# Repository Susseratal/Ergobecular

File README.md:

# Ergobecular Readme

## The Ergobecular  
The Ergobecular is a layout for a customisable, ergonomic mechanical keyboard. While it's based on my personal layout and preferences, it's designed to be configured and customised to the needs and preferences of you, the user.  
One of the primary choices made is to focus on smaller key sizes, never going above 1.5 unit keys. This way, stabilisers are completely unneeded, which will make tuning them for acoustics much easier. 

The main choice will be whether you want a split board, or a plank. In the future, I'd like to create a kind of Alice like design, but for the time being these will be the two main options.  
In the split category, you'll also be able to choose between columnar and fully ortholinear, while the plank will just be fully ortho for standard case compatibility.  
You'll also need to choose whether you want MX compatible sockets, or Kailh choc compatible sockets. 

Once I've finished making the designs, you should be able to just grab the PCB files you want from this repo and upload them to your PCB manufacturer of choice.  
Finally, I'll have not only firmware source files for you to start from, I'll also have a precompiled hex file for you to flash straight to the board if you don't have QMK configured, and don't mind using my layout. 

When the project is further along, a proper build guide will be available here as well. 

## The EBSplit  
The split version of the Ergobecular is probably the most customisable, as not only does it have options for all the different switches, you can also choose between columnar or fully ortho.  

This version of the board is likely going to be more ergonomic than the plank version, and more versatile if you've got the setup to handle it, but less portable.  
It'll need an extra TRRS cable to connect the halves, and you'll have to remember to carry around both halves of it, plus additional unpacking time.  
If you're the type of person who moves between home and the office, this might not be the way to go. 

I'd like to include a small screen for displaying information in this version, as I like the idea of having it pull system time, as well as displaying layer information.  
I think it could even be used for fun little gimmicks like a compass or something, I'm not sure. Being programmable, I'm sure people will be able to think of some fun stuff to do with this. 

## The EBPlank  
The plank version is designed either for someone who's not so fussed about a split design, or has a greater need for portability.  
While a split keyboard is portable, you can't quite throw it into a bag the same way you can with a regular keyboard.  

Because of this, as well as the slightly larger form factor, I see this as being a slightly more beginner friendly variant of the board.  
A stepping stone for someone who's tentatively interested in building their own keyboard, and wants to try a non-staggered layout, but isn't fully ready to commit to the split.  
This will also help someone get more used to designing their own layouts, although it would definitely be easier to get a ZSA keyboard, as their online layout tool is excellent, and very easy to use. 

I'm going to build one of these myself so that I can take it with me when I go away so I won't have to switch back to a more standard keyboard.  
Although that does mean I'm probably going to have to put silent switches in it.  

This will also be designed for compatibility with a lot of generic 60% cases, as this is a 60% keeb, rather than the split variant which is closer to a 40%.  
The case I'll be using for reference is a Miller GM862 which I've got sat on my shelf, but I'm going to try and include screw holes in standard places where possible.  
If you run into any issues with aftermarket cases, please send me an email to let me know.  
If it's just a one off thing I can't promise I'll be able to do much, but if I get multiple people telling me it doesn't fit common cases I'll definitely see what i can do. 

## Firmware  
The firmware has moved! I'm no longer keeping my firmware source here, rather I am including the source, as well as the precompiled binaries for all my keyboard layouts in [my own fork of the QMK firmware](https://github.com/susseratal/qmk_firmware)! 

My Ergodox is the Shine variant, so if you have the Glow or non LED variants, it might be prudent to download the necessary firmware and do a diff to see where changes need to be made.  
Also if you've got a Moonlander, you might also have to make some tweaks to the layout in order to make it work. I've been meaning to make versions of my layout for these keyboards too, but it's just a matter of finding the time. 

The difference between my firmware, and the version of my Ergodox layout available on ZSA's online configurator is that I've got a set of custom macro functions to make typing and editing text more "vim" like. The Oryx configurator does not, unfortunately, have support for layer switch on macro.  

My standard for laying out the firmware is that each column should be 3 spaces away from the longest line on the previous column. This should make it easier to read.  

## Todo:  
 
        - [ ] Design variants for 
                - [ ] split columnar MX 
                - [ ] split ortho MX
                - [ ] split columnar Choc
                - [ ] split ortho Choc
                - [ ] Plank MX
                - [ ] Plank Choc
        - [ ] Design and compile firmware for all of these
        - [ ] Design cases and plates for 3D printing

## Done:

        - [x] Write a design brief
        - [x] Custom qmk fork :)

Please do get in touch and let me know what you think of the designs and if you've used any of them. (when they're done of course) Feedback is always appreciated. 

Cheers,  
~ Iain xx

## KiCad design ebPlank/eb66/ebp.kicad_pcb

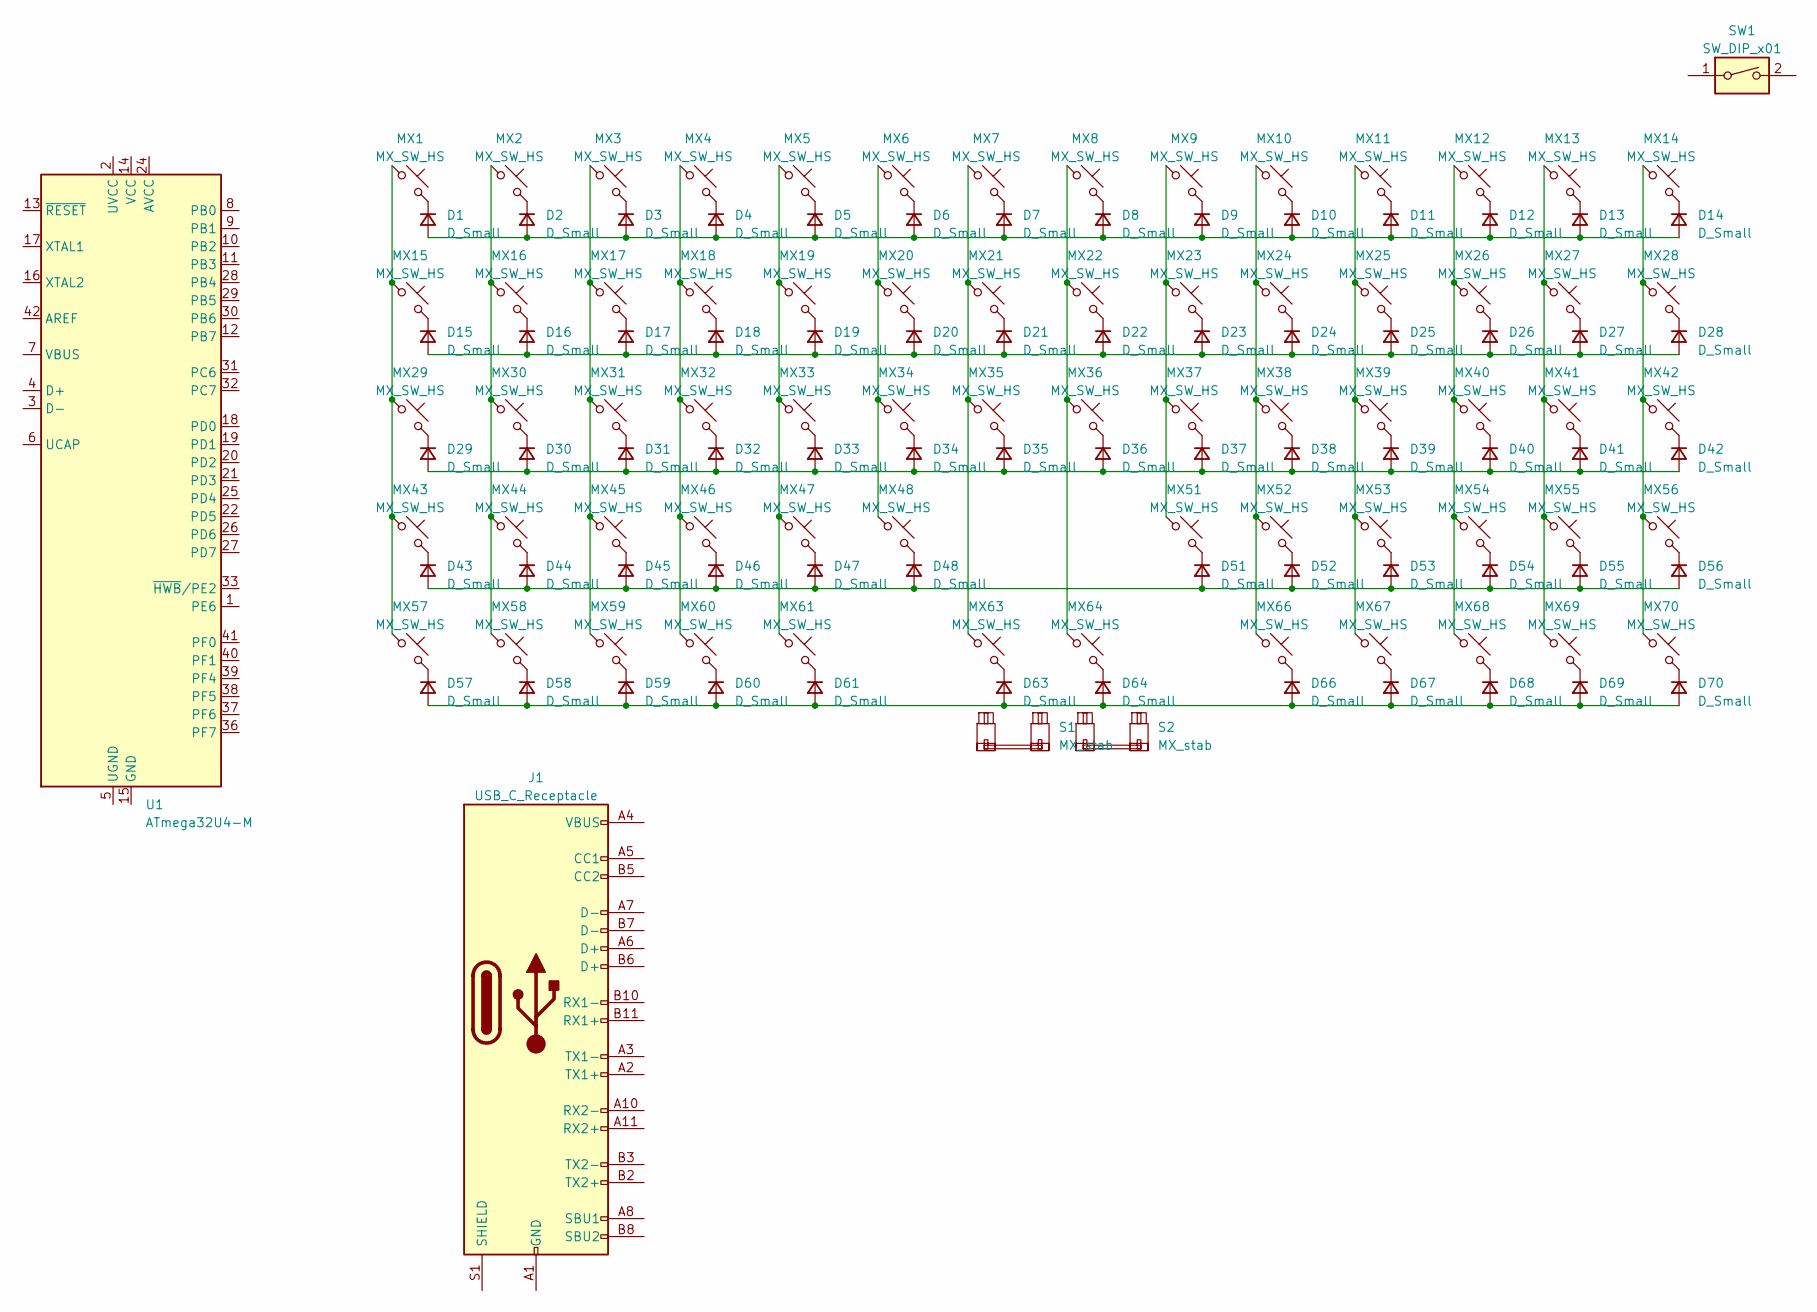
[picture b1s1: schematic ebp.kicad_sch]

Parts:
D1, D2, D3, D4, D5, D6, D7, D8, D9, D10, D11, D12, D13, D14, D15, D16, D17, D18, D19, D20, D21, D22, D23, D24, D25, D26, D27, D28, D29, D30, D31, D32, D33, D34, D35, D36, D37, D38, D39, D40, D41, D42, D43, D44, D45, D46, D47, D48, D51, D52, D53, D54, D55, D56, D57, D58, D59, D60, D61, D63, D64, D66, D67, D68, D69, D70: D_Small; D_SOD-123
J1: USB_C_Receptacle; USB_C_Receptacle_HRO_TYPE-C-31-M-14
MX1, MX14, MX15, MX21, MX22, MX28, MX29, MX35, MX36, MX42, MX43, MX56, MX57, MX70: MX_SW_HS; SW_MX_HS_1.5u
MX2, MX3, MX4, MX5, MX6, MX7, MX8, MX9, MX10, MX11, MX12, MX13, MX16, MX17, MX18, MX19, MX20, MX23, MX24, MX25, MX26, MX27, MX30, MX31, MX32, MX33, MX34, MX37, MX38, MX39, MX40, MX41, MX44, MX45, MX46, MX47, MX48, MX51, MX52, MX53, MX54, MX55, MX58, MX59, MX60, MX61, MX63, MX64, MX66, MX67, MX68, MX69: MX_SW_HS; SW_MX_HS_1u
S1, S2: MX_stab; STAB_MX_P_2u
SW1: SW_DIP_x01; SW_SKHLLCA010
U1: ATmega32U4-M; QFN-44-1EP_7x7mm_P0.5mm_EP5.2x5.2mm

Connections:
unnamed: D1.2 (A), D2.2 (A), D3.2 (A), D4.2 (A), D5.2 (A), D6.2 (A), D7.2 (A), D8.2 (A), D9.2 (A), D10.2 (A), D11.2 (A), D12.2 (A), D13.2 (A), D14.2 (A)
unnamed: D1.1 (K), MX1.2
unnamed: D2.1 (K), MX2.2
unnamed: D3.1 (K), MX3.2
unnamed: D4.1 (K), MX4.2
unnamed: D5.1 (K), MX5.2
unnamed: D6.1 (K), MX6.2
unnamed: D7.1 (K), MX7.2
unnamed: D8.1 (K), MX8.2
unnamed: D9.1 (K), MX9.2
unnamed: D10.1 (K), MX10.2
unnamed: D11.1 (K), MX11.2
unnamed: D12.1 (K), MX12.2
unnamed: D13.1 (K), MX13.2
unnamed: D14.1 (K), MX14.2
unnamed: D15.2 (A), D16.2 (A), D17.2 (A), D18.2 (A), D19.2 (A), D20.2 (A), D21.2 (A), D22.2 (A), D23.2 (A), D24.2 (A), D25.2 (A), D26.2 (A), D27.2 (A), D28.2 (A)
unnamed: D15.1 (K), MX15.2
unnamed: D16.1 (K), MX16.2
unnamed: D17.1 (K), MX17.2
unnamed: D18.1 (K), MX18.2
unnamed: D19.1 (K), MX19.2
unnamed: D20.1 (K), MX20.2
unnamed: D21.1 (K), MX21.2
unnamed: D22.1 (K), MX22.2
unnamed: D23.1 (K), MX23.2
unnamed: D24.1 (K), MX24.2
unnamed: D25.1 (K), MX25.2
unnamed: D26.1 (K), MX26.2
unnamed: D27.1 (K), MX27.2
unnamed: D28.1 (K), MX28.2
unnamed: D29.2 (A), D30.2 (A), D31.2 (A), D32.2 (A), D33.2 (A), D34.2 (A), D35.2 (A), D36.2 (A), D37.2 (A), D38.2 (A), D39.2 (A), D40.2 (A), D41.2 (A), D42.2 (A)
unnamed: D29.1 (K), MX29.2
unnamed: D30.1 (K), MX30.2
unnamed: D31.1 (K), MX31.2
unnamed: D32.1 (K), MX32.2
unnamed: D33.1 (K), MX33.2
unnamed: D34.1 (K), MX34.2
unnamed: D35.1 (K), MX35.2
unnamed: D36.1 (K), MX36.2
unnamed: D37.1 (K), MX37.2
unnamed: D38.1 (K), MX38.2
unnamed: D39.1 (K), MX39.2
unnamed: D40.1 (K), MX40.2
unnamed: D41.1 (K), MX41.2
unnamed: D42.1 (K), MX42.2
unnamed: D43.2 (A), D44.2 (A), D45.2 (A), D46.2 (A), D47.2 (A), D48.2 (A), D51.2 (A), D52.2 (A), D53.2 (A), D54.2 (A), D55.2 (A), D56.2 (A)
unnamed: D43.1 (K), MX43.2
unnamed: D44.1 (K), MX44.2
unnamed: D45.1 (K), MX45.2
unnamed: D46.1 (K), MX46.2
unnamed: D47.1 (K), MX47.2
unnamed: D48.1 (K), MX48.2
unnamed: D51.1 (K), MX51.2
unnamed: D52.1 (K), MX52.2
unnamed: D53.1 (K), MX53.2
unnamed: D54.1 (K), MX54.2
unnamed: D55.1 (K), MX55.2
unnamed: D56.1 (K), MX56.2
unnamed: D57.2 (A), D58.2 (A), D59.2 (A), D60.2 (A), D61.2 (A), D63.2 (A), D64.2 (A), D66.2 (A), D67.2 (A), D68.2 (A), D69.2 (A), D70.2 (A)
unnamed: D57.1 (K), MX57.2
unnamed: D58.1 (K), MX58.2
unnamed: D59.1 (K), MX59.2
unnamed: D60.1 (K), MX60.2
unnamed: D61.1 (K), MX61.2
unnamed: D63.1 (K), MX63.2
unnamed: D64.1 (K), MX64.2
unnamed: D66.1 (K), MX66.2
unnamed: D67.1 (K), MX67.2
unnamed: D68.1 (K), MX68.2
unnamed: D69.1 (K), MX69.2
unnamed: D70.1 (K), MX70.2
unnamed: J1.A1 (GND), J1.A12 (GND), J1.B1 (GND), J1.B12 (GND)
unnamed: J1.A4 (VBUS), J1.A9 (VBUS), J1.B4 (VBUS), J1.B9 (VBUS)
unnamed: MX1.1, MX15.1, MX29.1, MX43.1, MX57.1
unnamed: MX10.1, MX24.1, MX38.1, MX52.1, MX66.1
unnamed: MX11.1, MX25.1, MX39.1, MX53.1, MX67.1
unnamed: MX12.1, MX26.1, MX40.1, MX54.1, MX68.1
unnamed: MX13.1, MX27.1, MX41.1, MX55.1, MX69.1
unnamed: MX14.1, MX28.1, MX42.1, MX56.1, MX70.1
unnamed: MX2.1, MX16.1, MX30.1, MX44.1, MX58.1
unnamed: MX3.1, MX17.1, MX31.1, MX45.1, MX59.1
unnamed: MX4.1, MX18.1, MX32.1, MX46.1, MX60.1
unnamed: MX5.1, MX19.1, MX33.1, MX47.1, MX61.1
unnamed: MX6.1, MX20.1, MX34.1, MX48.1
unnamed: MX7.1, MX21.1, MX35.1, MX63.1
unnamed: MX8.1, MX22.1, MX36.1, MX64.1
unnamed: MX9.1, MX23.1, MX37.1, MX51.1
unnamed: U1.24 (AVCC), U1.44 (AVCC)
unnamed: U1.15 (GND), U1.23 (GND), U1.35 (GND), U1.43 (GND), U1.45 (GND)
unnamed: U1.14 (VCC), U1.34 (VCC)

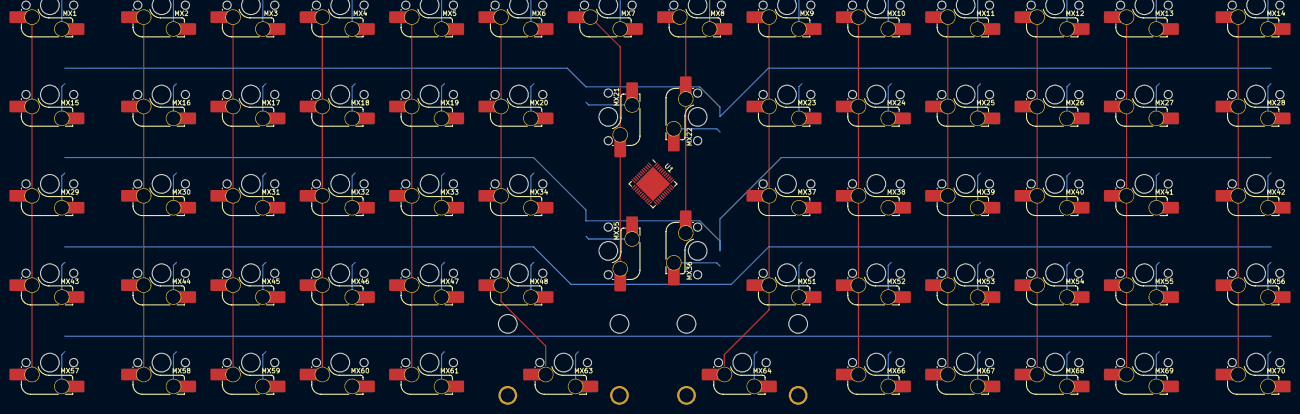
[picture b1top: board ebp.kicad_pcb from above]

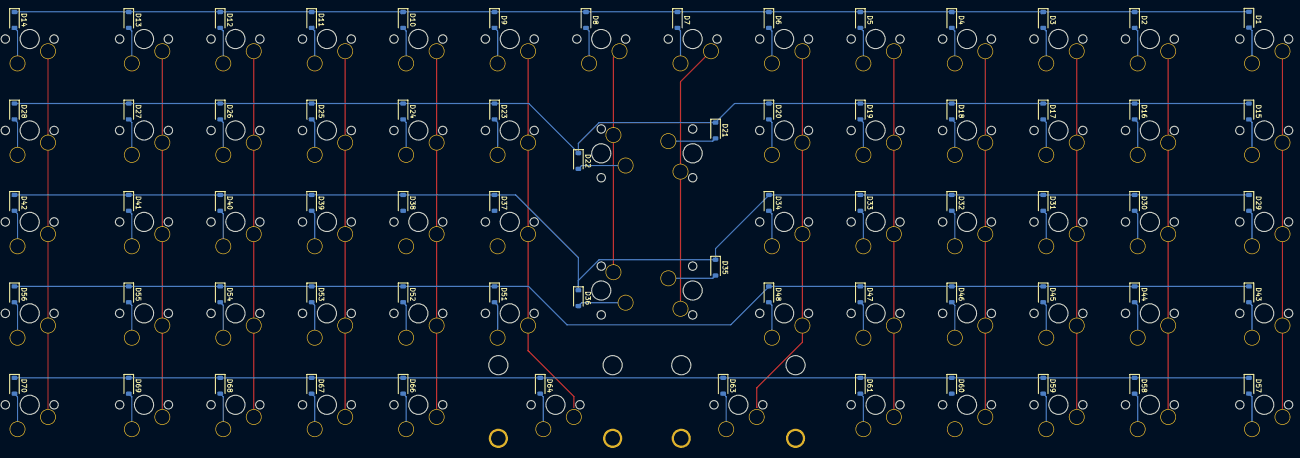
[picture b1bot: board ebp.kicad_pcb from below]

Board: 2 copper layers, 135 parts (66 on the bottom side), 88 nets.

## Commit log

2022-06-06 created license
2022-06-08 added two directories
2022-06-17 added readme
2022-08-03 added ergodox firmware
2022-08-03 I always forget the double space in MD
2022-08-03 placed erephyx source into src folder
2022-08-03 added image to readme
2022-08-03 updated readme image formatting
2022-08-04 updated erephyx keymap for ctrl+bspace macro on layer 1
2022-08-04 lowered tap-hold response time - now trying to get CAPS_WORD working
2022-08-05 lowered hold time and added caps word
2022-08-10 added more lighting controls and tidied up keymap
2022-09-05 added kicad files and updated RGB keys in Erephyx
2022-09-05 fixed a bug
2022-10-13 updated brackets on Ergodox
2022-10-13 fixed an innacurate keycode
2022-10-14 removed layer lighting from games layer
2022-10-14 added easy virtual desktop switch for windows
2022-11-04 made layer switch lighting more obvious
2022-11-07 added EBPlank75
2022-11-07 added empty firmware directory
2022-11-08 added images to readme
2022-11-28 rewrote readme and updated directories
2022-11-28 fixed an image naming error
2022-11-28 fixed a formatting error
2022-11-28 added vim-like visual select
2022-11-28 updated visual select
2022-11-30 moved firmware to qmk fork
2023-02-21 added kicad scheme for plank keeb
2023-05-06 updated ergobecular plank to eb66
